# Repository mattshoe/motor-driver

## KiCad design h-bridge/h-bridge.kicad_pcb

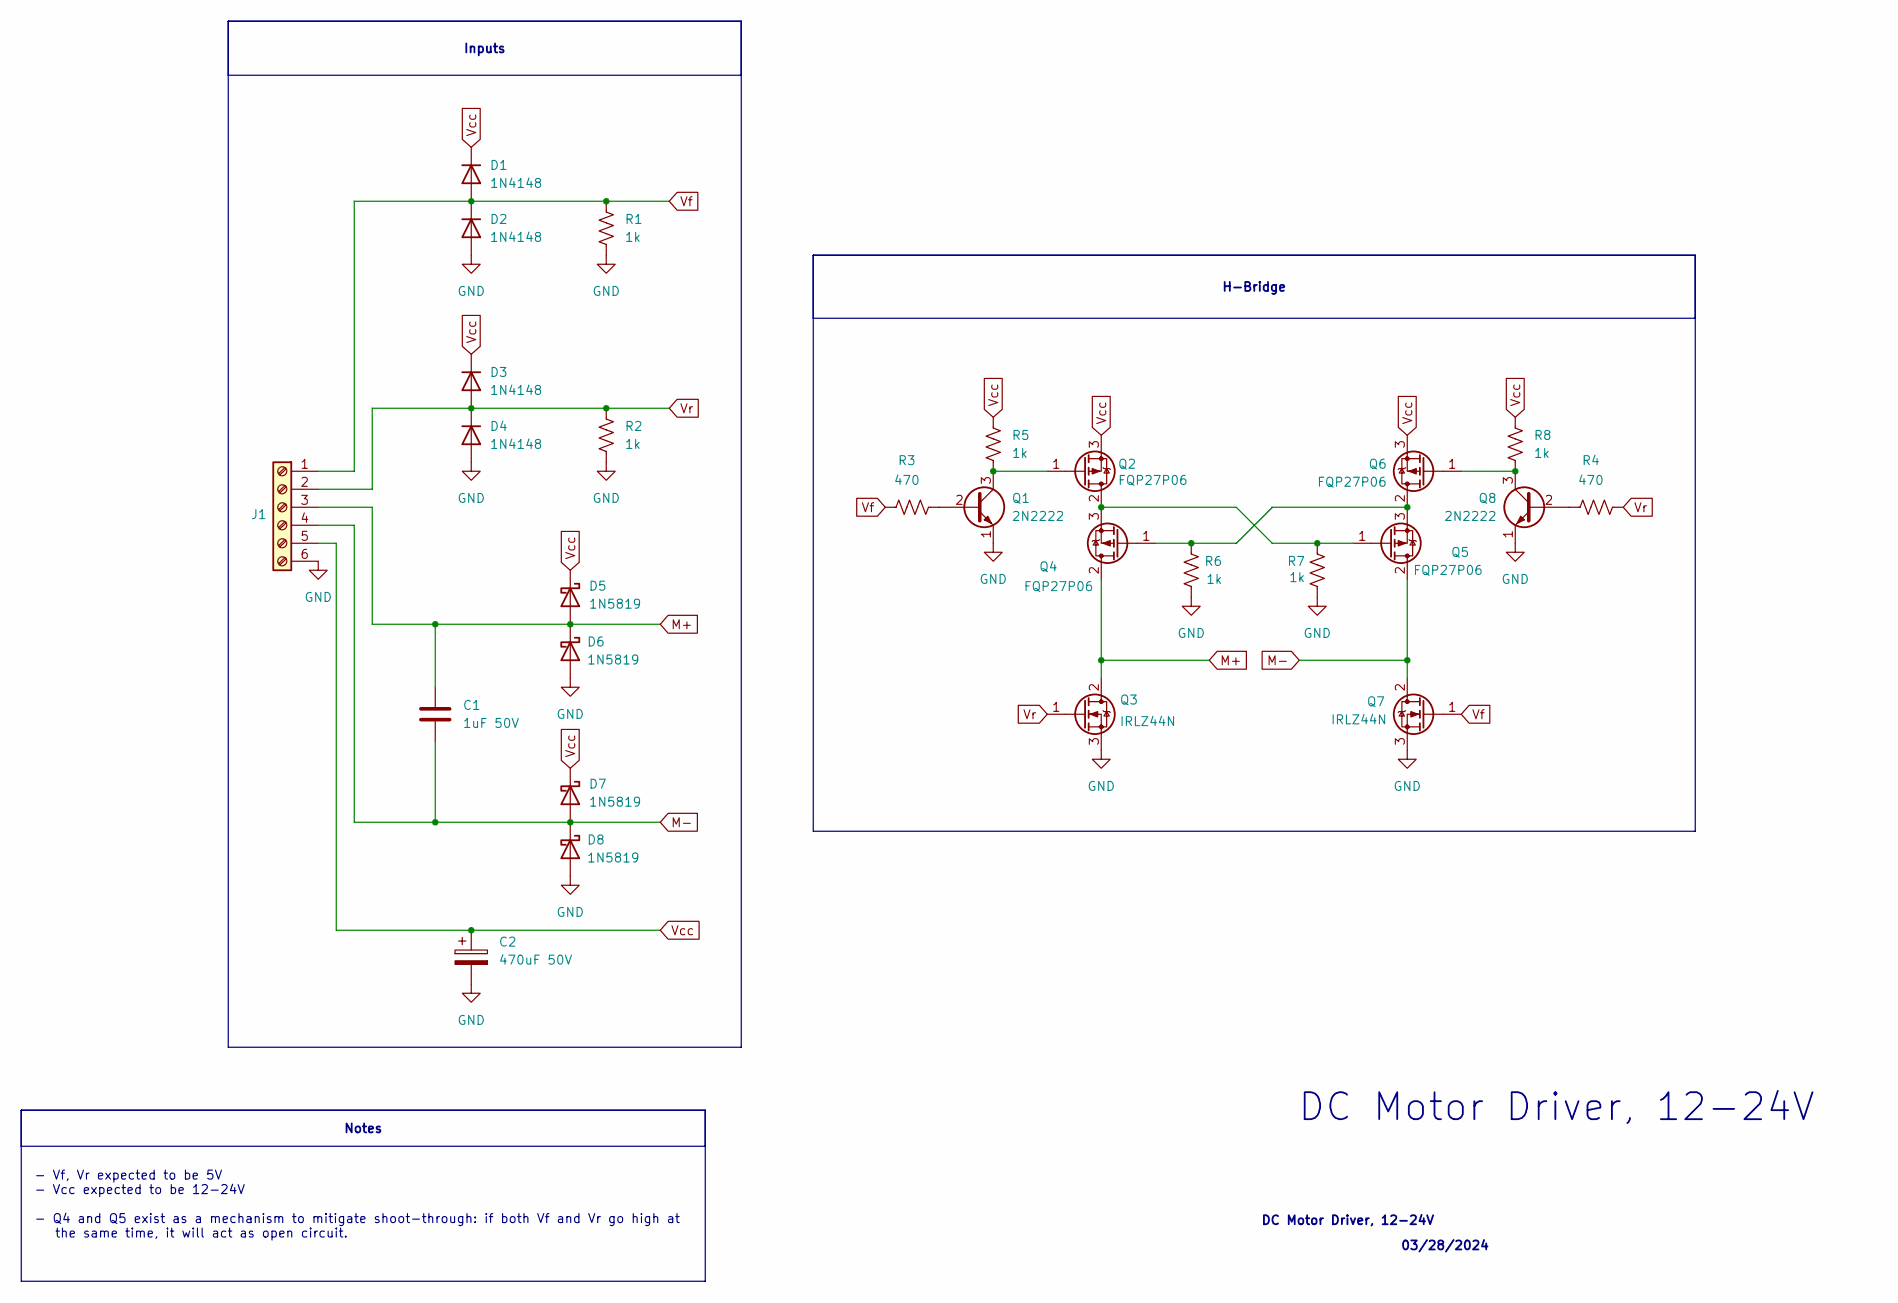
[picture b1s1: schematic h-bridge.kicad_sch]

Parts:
C1: 1uF 50V; C_Disc_D5.0mm_W2.5mm_P5.00mm
C2: 470uF 50V; CP_Radial_D8.0mm_P3.80mm
D1, D2, D3, D4: 1N4148; D_DO-35_SOD27_P7.62mm_Horizontal
D5, D6, D7, D8: 1N5819; D_DO-41_SOD81_P10.16mm_Horizontal
J1: Screw_Terminal_01x06; TerminalBlock_Xinya_XY308-2.54-6P_1x06_P2.54mm_Horizontal
Q1, Q8: 2N2222; TO-92_HandSolder
Q2, Q4, Q5, Q6: FQP27P06; TO-220-3_Vertical
Q3, Q7: IRLZ44N; TO-220-3_Vertical
R1, R2, R5, R6, R7, R8: 1k; R_Axial_DIN0207_L6.3mm_D2.5mm_P10.16mm_Horizontal
R3, R4: 470; R_Axial_DIN0207_L6.3mm_D2.5mm_P10.16mm_Horizontal

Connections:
GND: C2.2, D2.2 (A), D4.2 (A), D6.2 (A), D8.2 (A), J1.6, Q1.1 (E), Q3.3 (S), Q7.3 (S), Q8.1 (E), R1.2, R2.2, R6.2, R7.2
M+: C1.1, D5.2 (A), D6.1 (K), J1.3, Q3.2 (D), Q4.2 (D)
M-: C1.2, D7.2 (A), D8.1 (K), J1.4, Q5.2 (D), Q7.2 (D)
unnamed: Q1.2 (B), R3.2
unnamed: Q1.3 (C), Q2.1 (G), R5.2
unnamed: Q2.2 (D), Q4.3 (S), Q5.1 (G), R7.1
unnamed: Q4.1 (G), Q5.3 (S), Q6.2 (D), R6.1
unnamed: Q6.1 (G), Q8.3 (C), R8.2
unnamed: Q8.2 (B), R4.1
Vcc: C2.1, D1.1 (K), D3.1 (K), D5.1 (K), D7.1 (K), J1.5, Q2.3 (S), Q6.3 (S), R5.1, R8.1
Vf: D1.2 (A), D2.1 (K), J1.1, Q7.1 (G), R1.1, R3.1
Vr: D3.2 (A), D4.1 (K), J1.2, Q3.1 (G), R2.1, R4.2

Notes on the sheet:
DC Motor Driver, 12-24V
03/28/2024
- Vf, Vr expected to be 5V - Vcc expected to be 12-24V - Q4 and Q5 exist as a mechanism to mitigate shoot-through: if both Vf and Vr go high at the same time, it will act as open circuit.
H-Bridge
Inputs
Notes

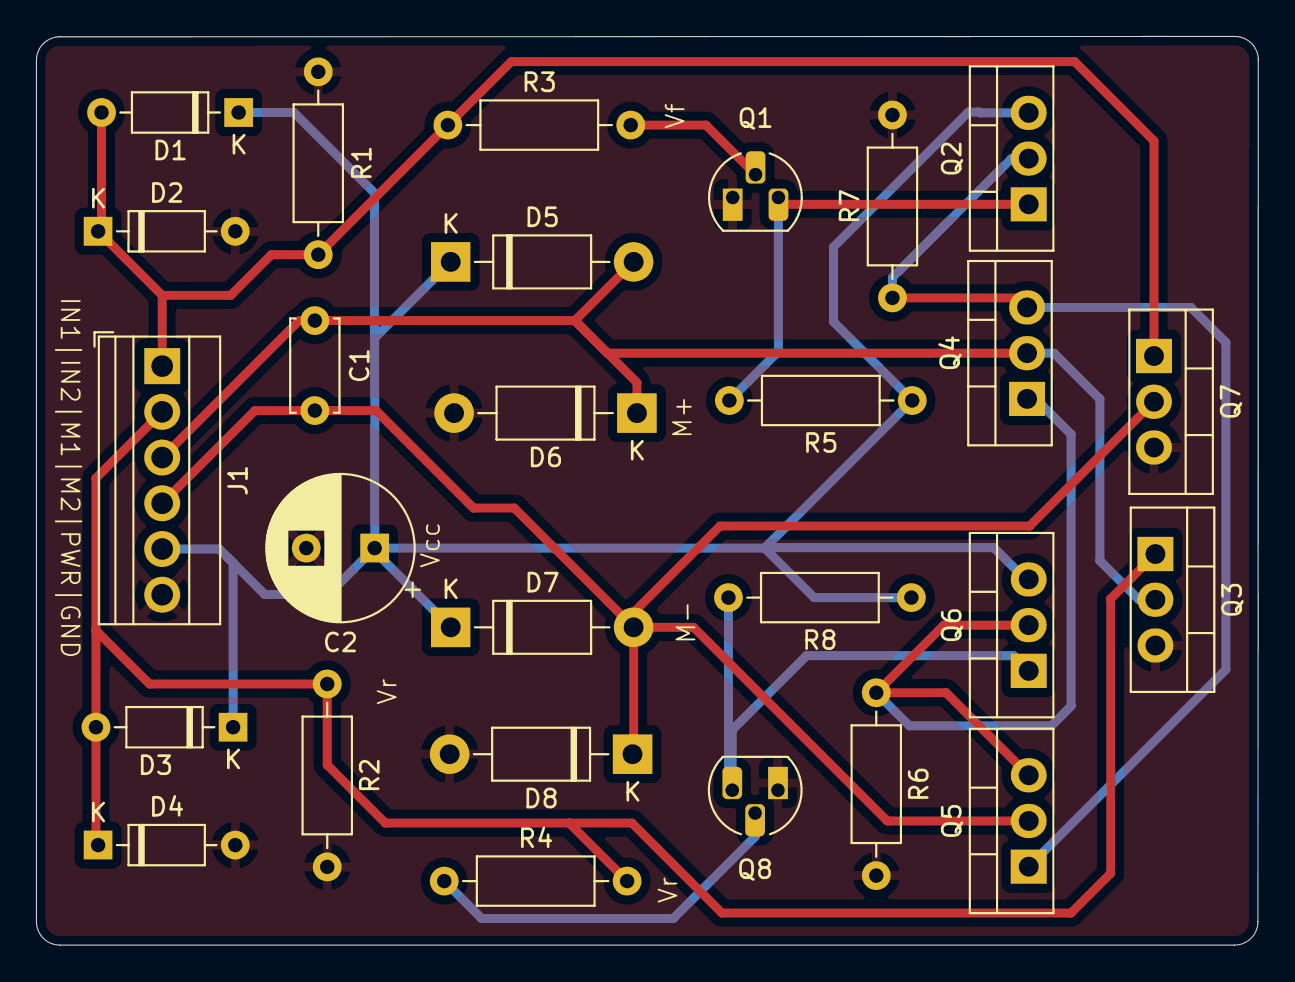
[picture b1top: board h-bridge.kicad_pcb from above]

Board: 2 copper layers, 67.9 x 50.5 mm, 27 parts (0 on the bottom side), 12 nets.

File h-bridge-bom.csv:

"Reference","Value","Datasheet","Footprint","Qty","DNP"
"C1","1uF 50V","~","Capacitor_THT:C_Disc_D5.0mm_W2.5mm_P5.00mm","1",""
"C2","470uF 50V","~","Capacitor_THT:CP_Radial_D8.0mm_P3.80mm","1",""
"D1,D2,D3,D4","1N4148","https://assets.nexperia.com/documents/data-sheet/1N4148_1N4448.pdf","Diode_THT:D_DO-35_SOD27_P7.62mm_Horizontal","4",""
"D5,D6,D7,D8","1N5819","http://www.vishay.com/docs/88525/1n5817.pdf","Diode_THT:D_DO-41_SOD81_P10.16mm_Horizontal","4",""
"J1","Screw_Terminal_01x06","~","TerminalBlock:TerminalBlock_Xinya_XY308-2.54-6P_1x06_P2.54mm_Horizontal","1",""
"Q1,Q8","2N2222","http://www.onsemi.com/pub_link/Collateral/2N2219-D.PDF","Package_TO_SOT_THT:TO-92_Inline_Horizontal1","2",""
"Q2,Q4,Q5,Q6","IRF4905","http://www.infineon.com/dgdl/irf4905.pdf?fileId=5546d4625336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","Package_TO_SOT_THT:TO-220-3_Vertical","4",""
"Q3,Q7","IRLZ44N","http://www.irf.com/product-info/datasheets/data/irlz44n.pdf","Package_TO_SOT_THT:TO-220-3_Vertical","2",""
"R1,R2,R5,R6,R7,R8","1k","~","Resistor_THT:R_Axial_DIN0207_L6.3mm_D2.5mm_P10.16mm_Horizontal","6",""
"R3,R4","470","~","Resistor_THT:R_Axial_DIN0207_L6.3mm_D2.5mm_P10.16mm_Horizontal","2",""

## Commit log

2025-03-21 basic h-bridge implemented
2025-03-28 First POC
2025-03-28 Updated BOM
2025-03-28 Added screw terminal
2025-03-29 pcb layed out
2025-03-29 pcb routed
2025-03-29 gerber files done
2025-04-05 V2 Redesign Submitted to JLCPCB and BOM generated
2025-04-11 V3 submitted to JLCPCB
